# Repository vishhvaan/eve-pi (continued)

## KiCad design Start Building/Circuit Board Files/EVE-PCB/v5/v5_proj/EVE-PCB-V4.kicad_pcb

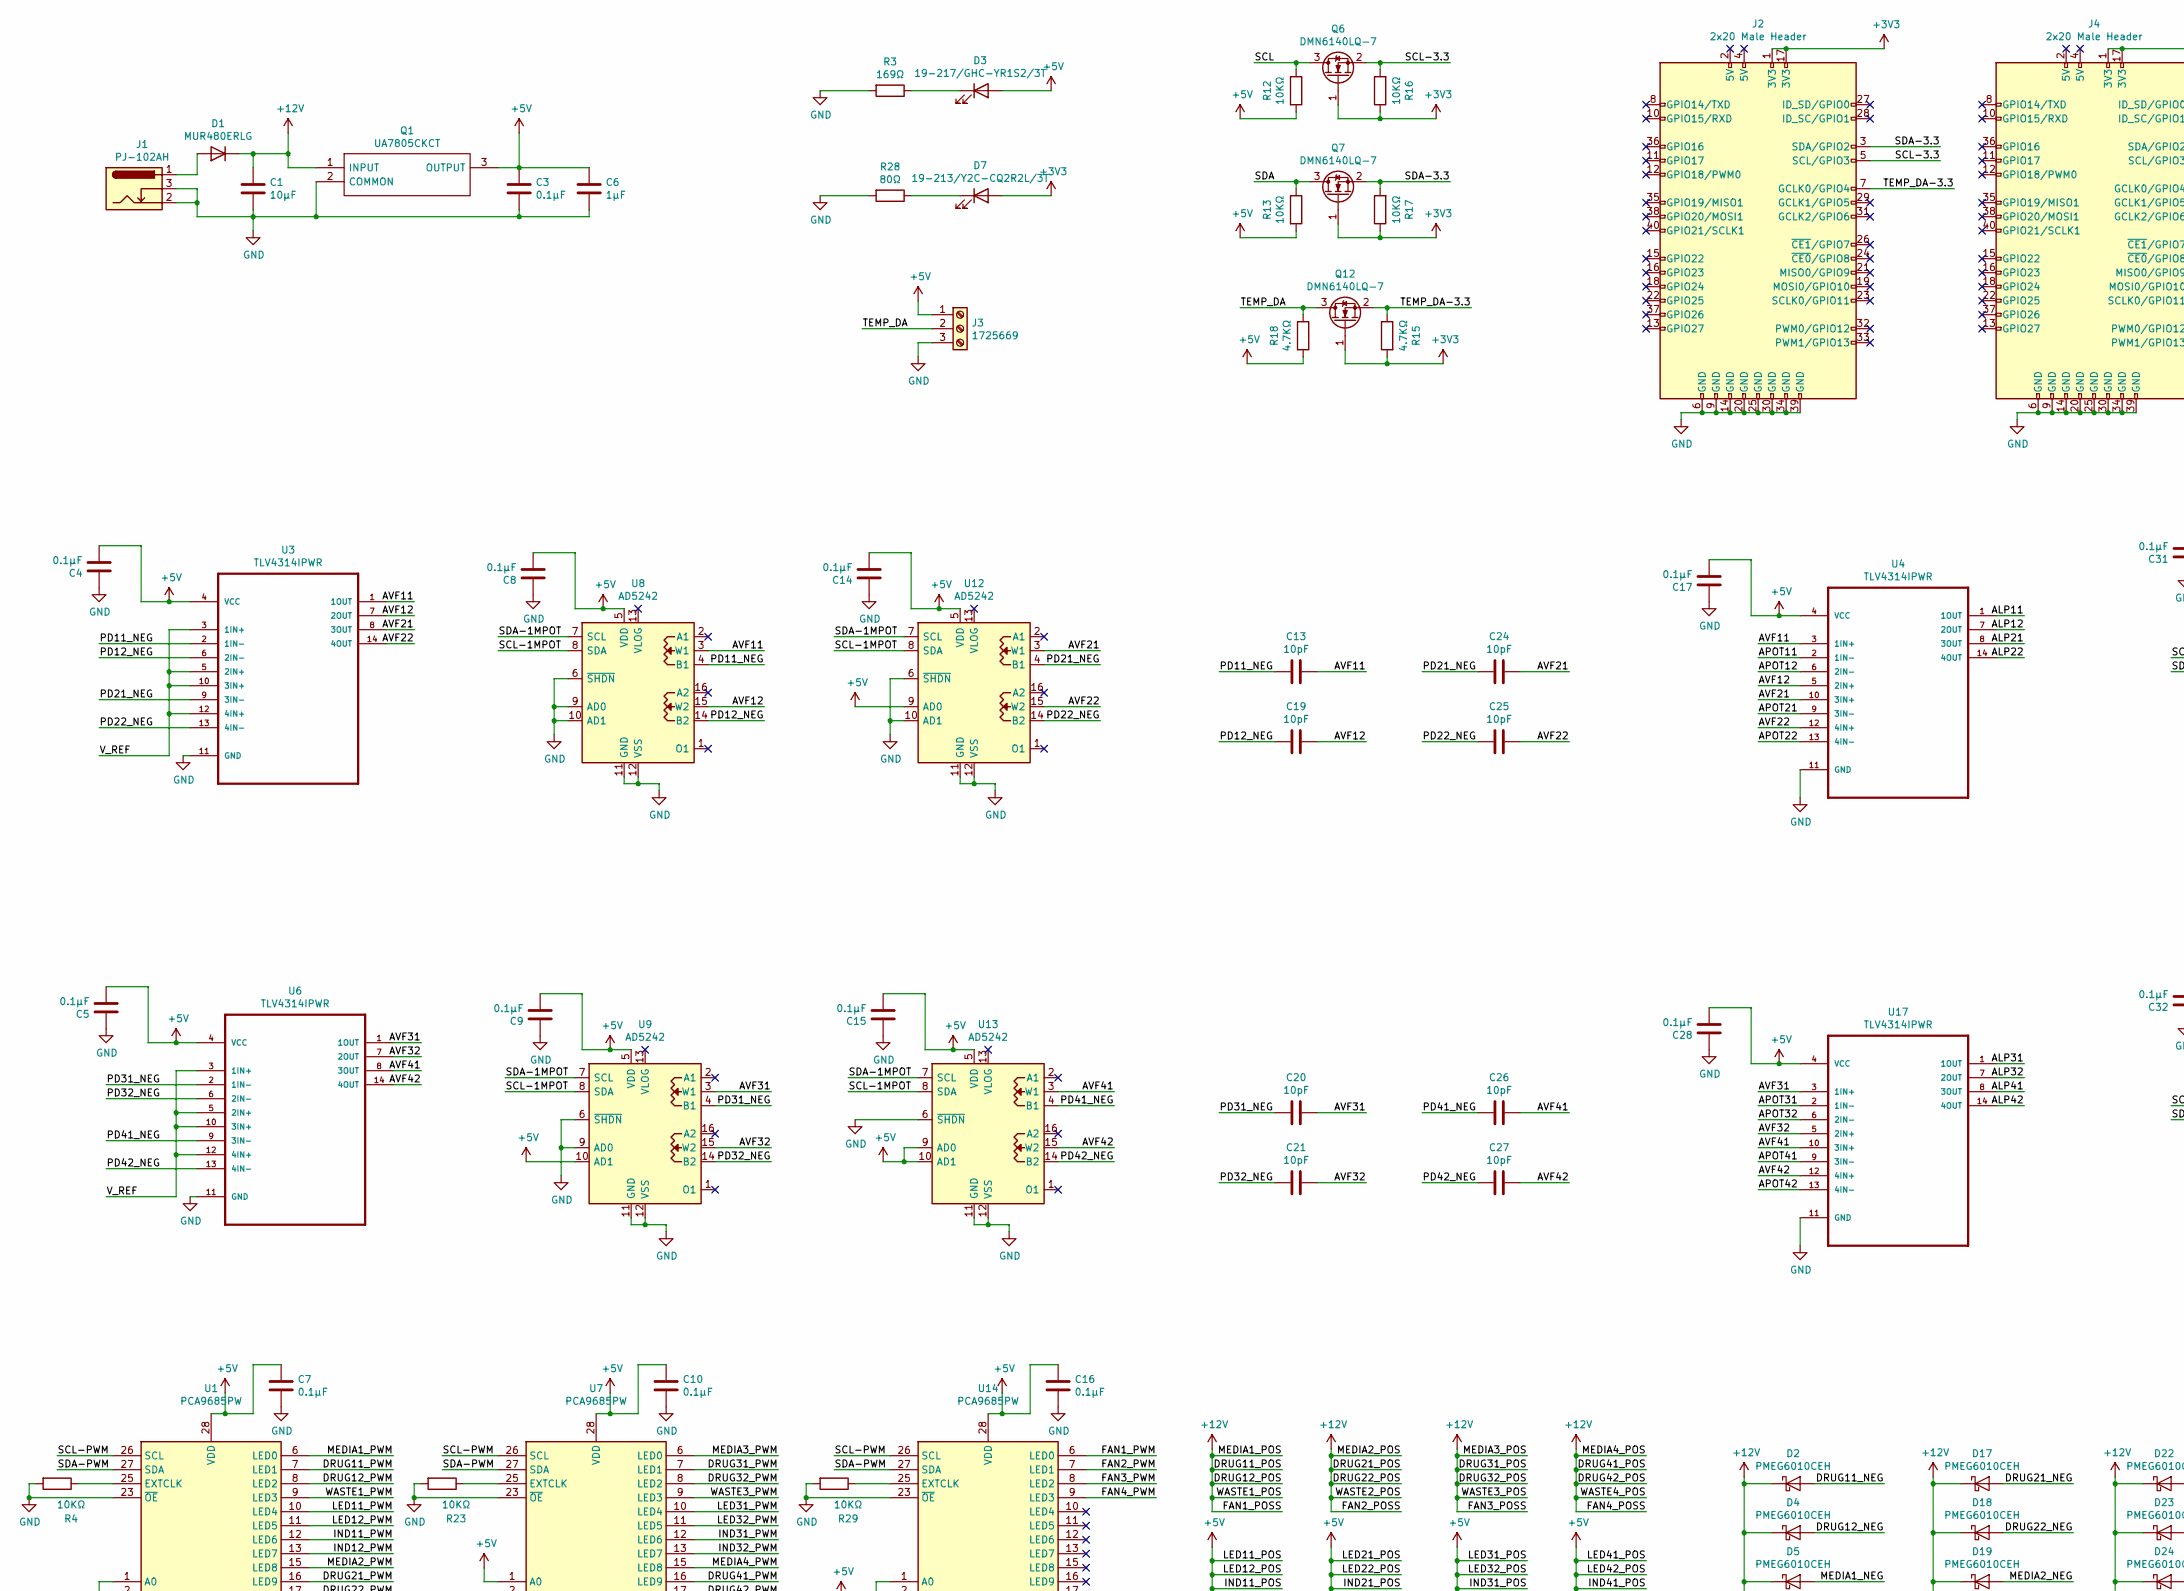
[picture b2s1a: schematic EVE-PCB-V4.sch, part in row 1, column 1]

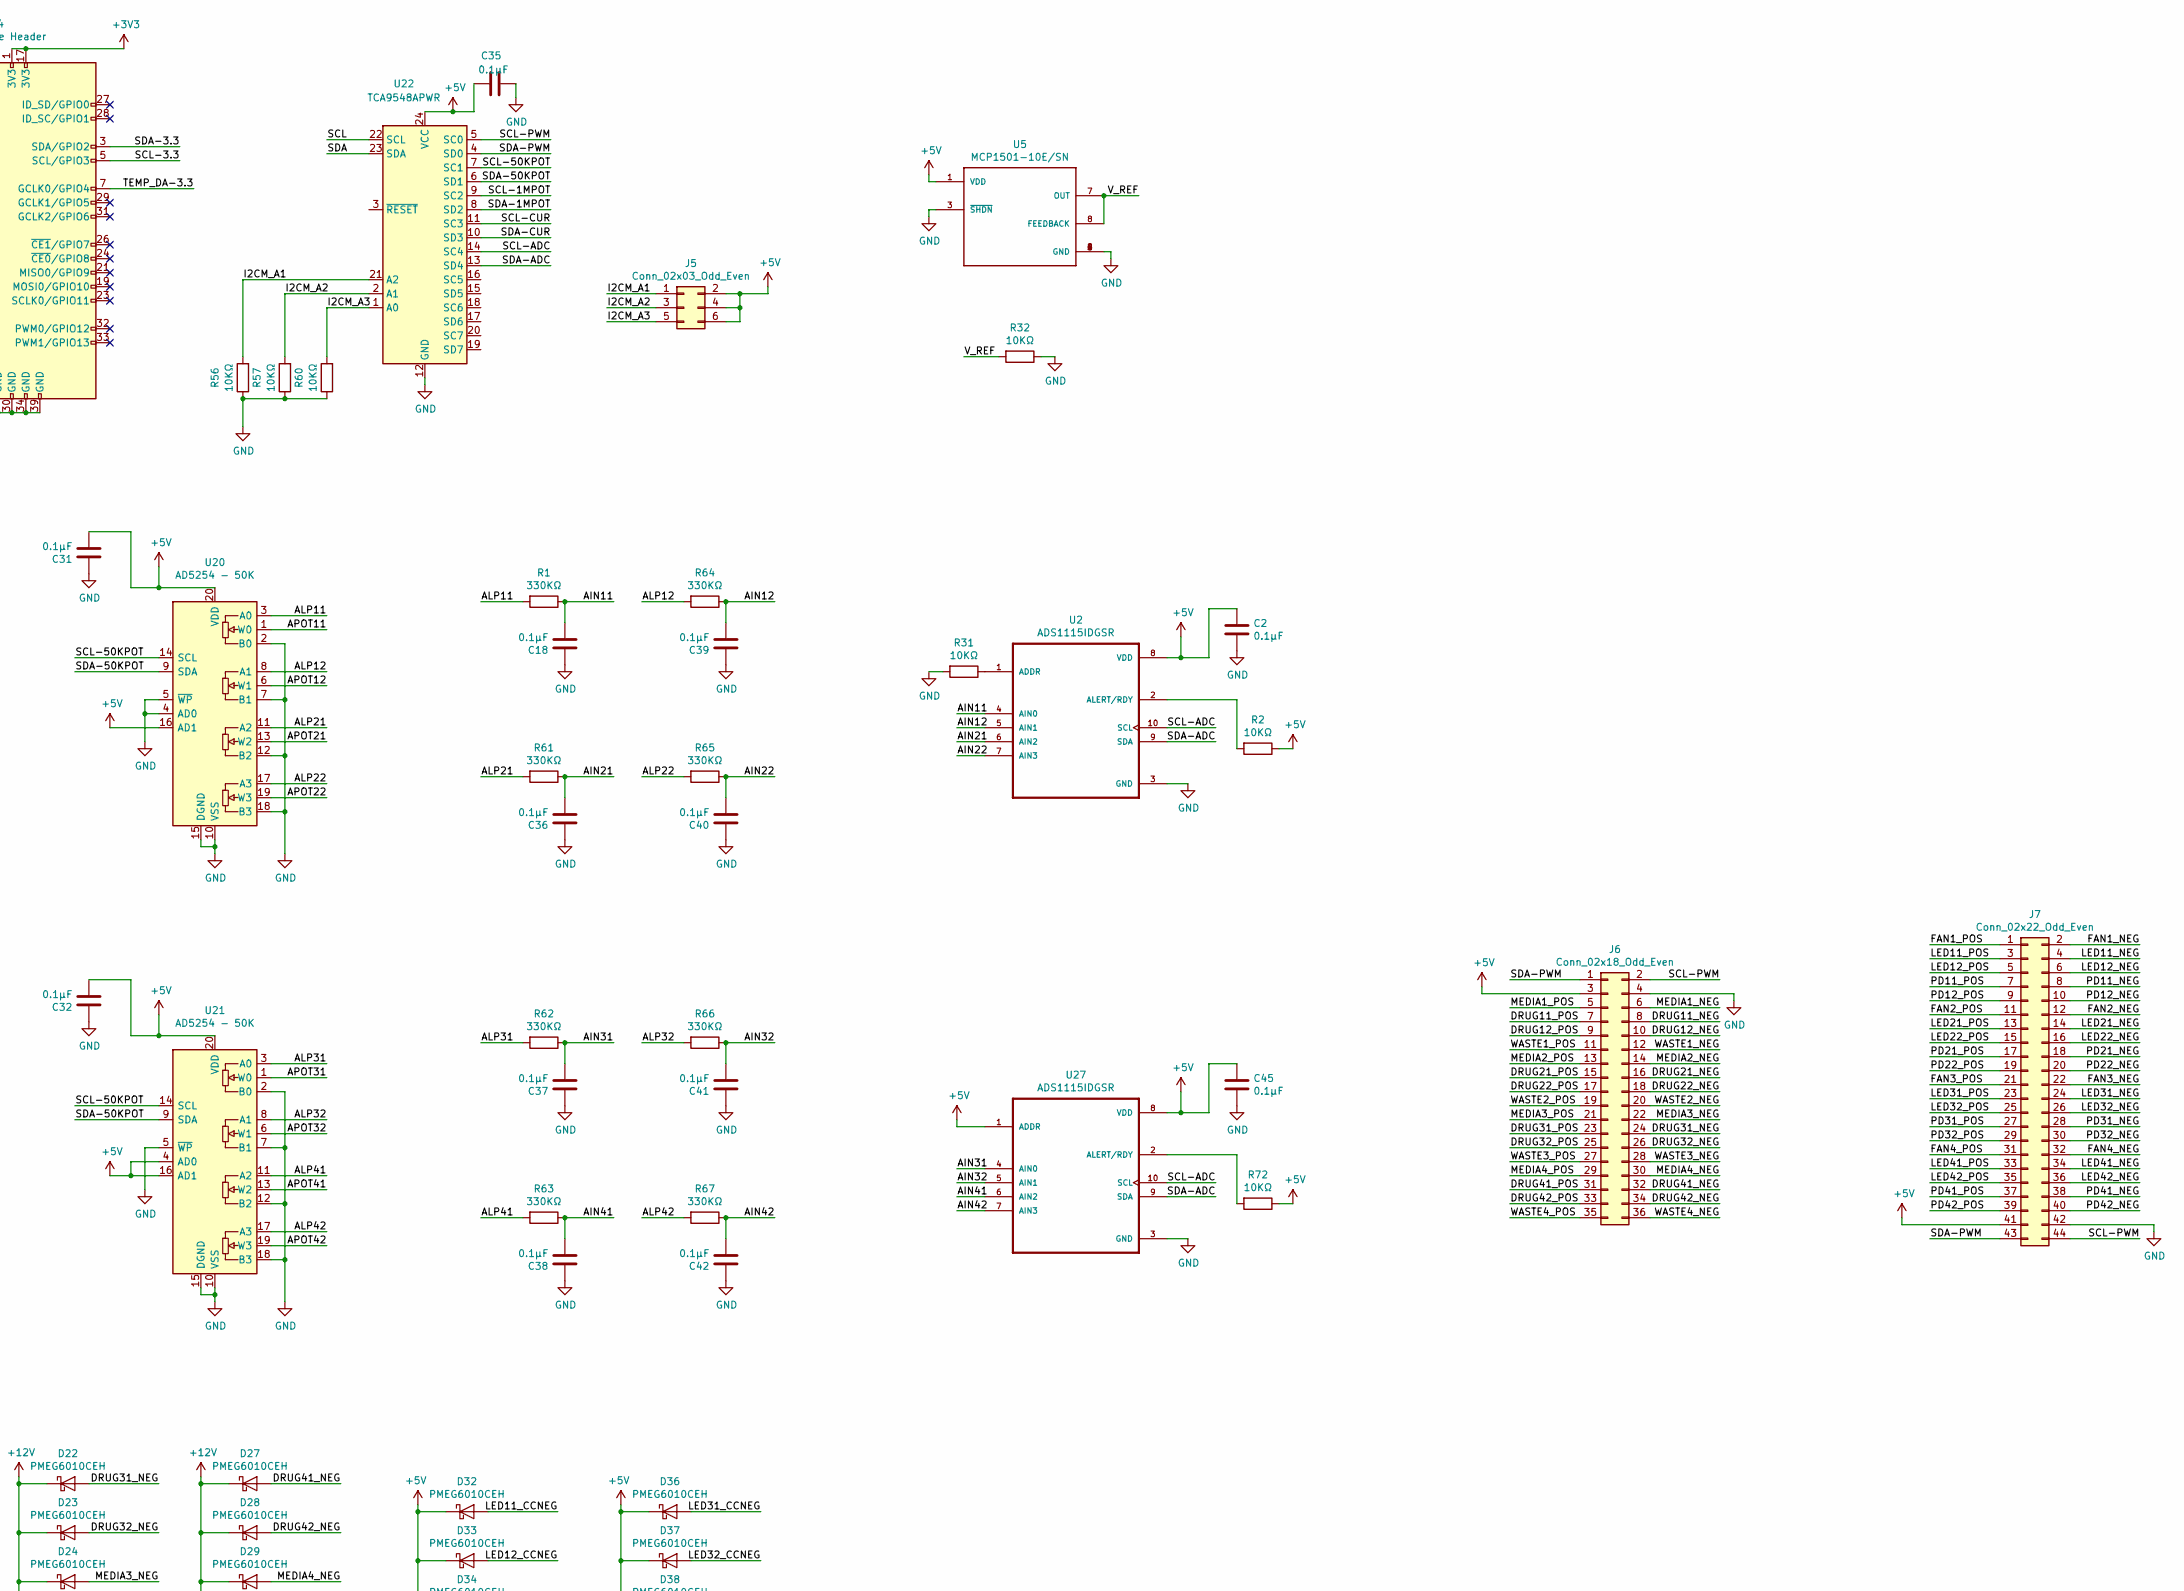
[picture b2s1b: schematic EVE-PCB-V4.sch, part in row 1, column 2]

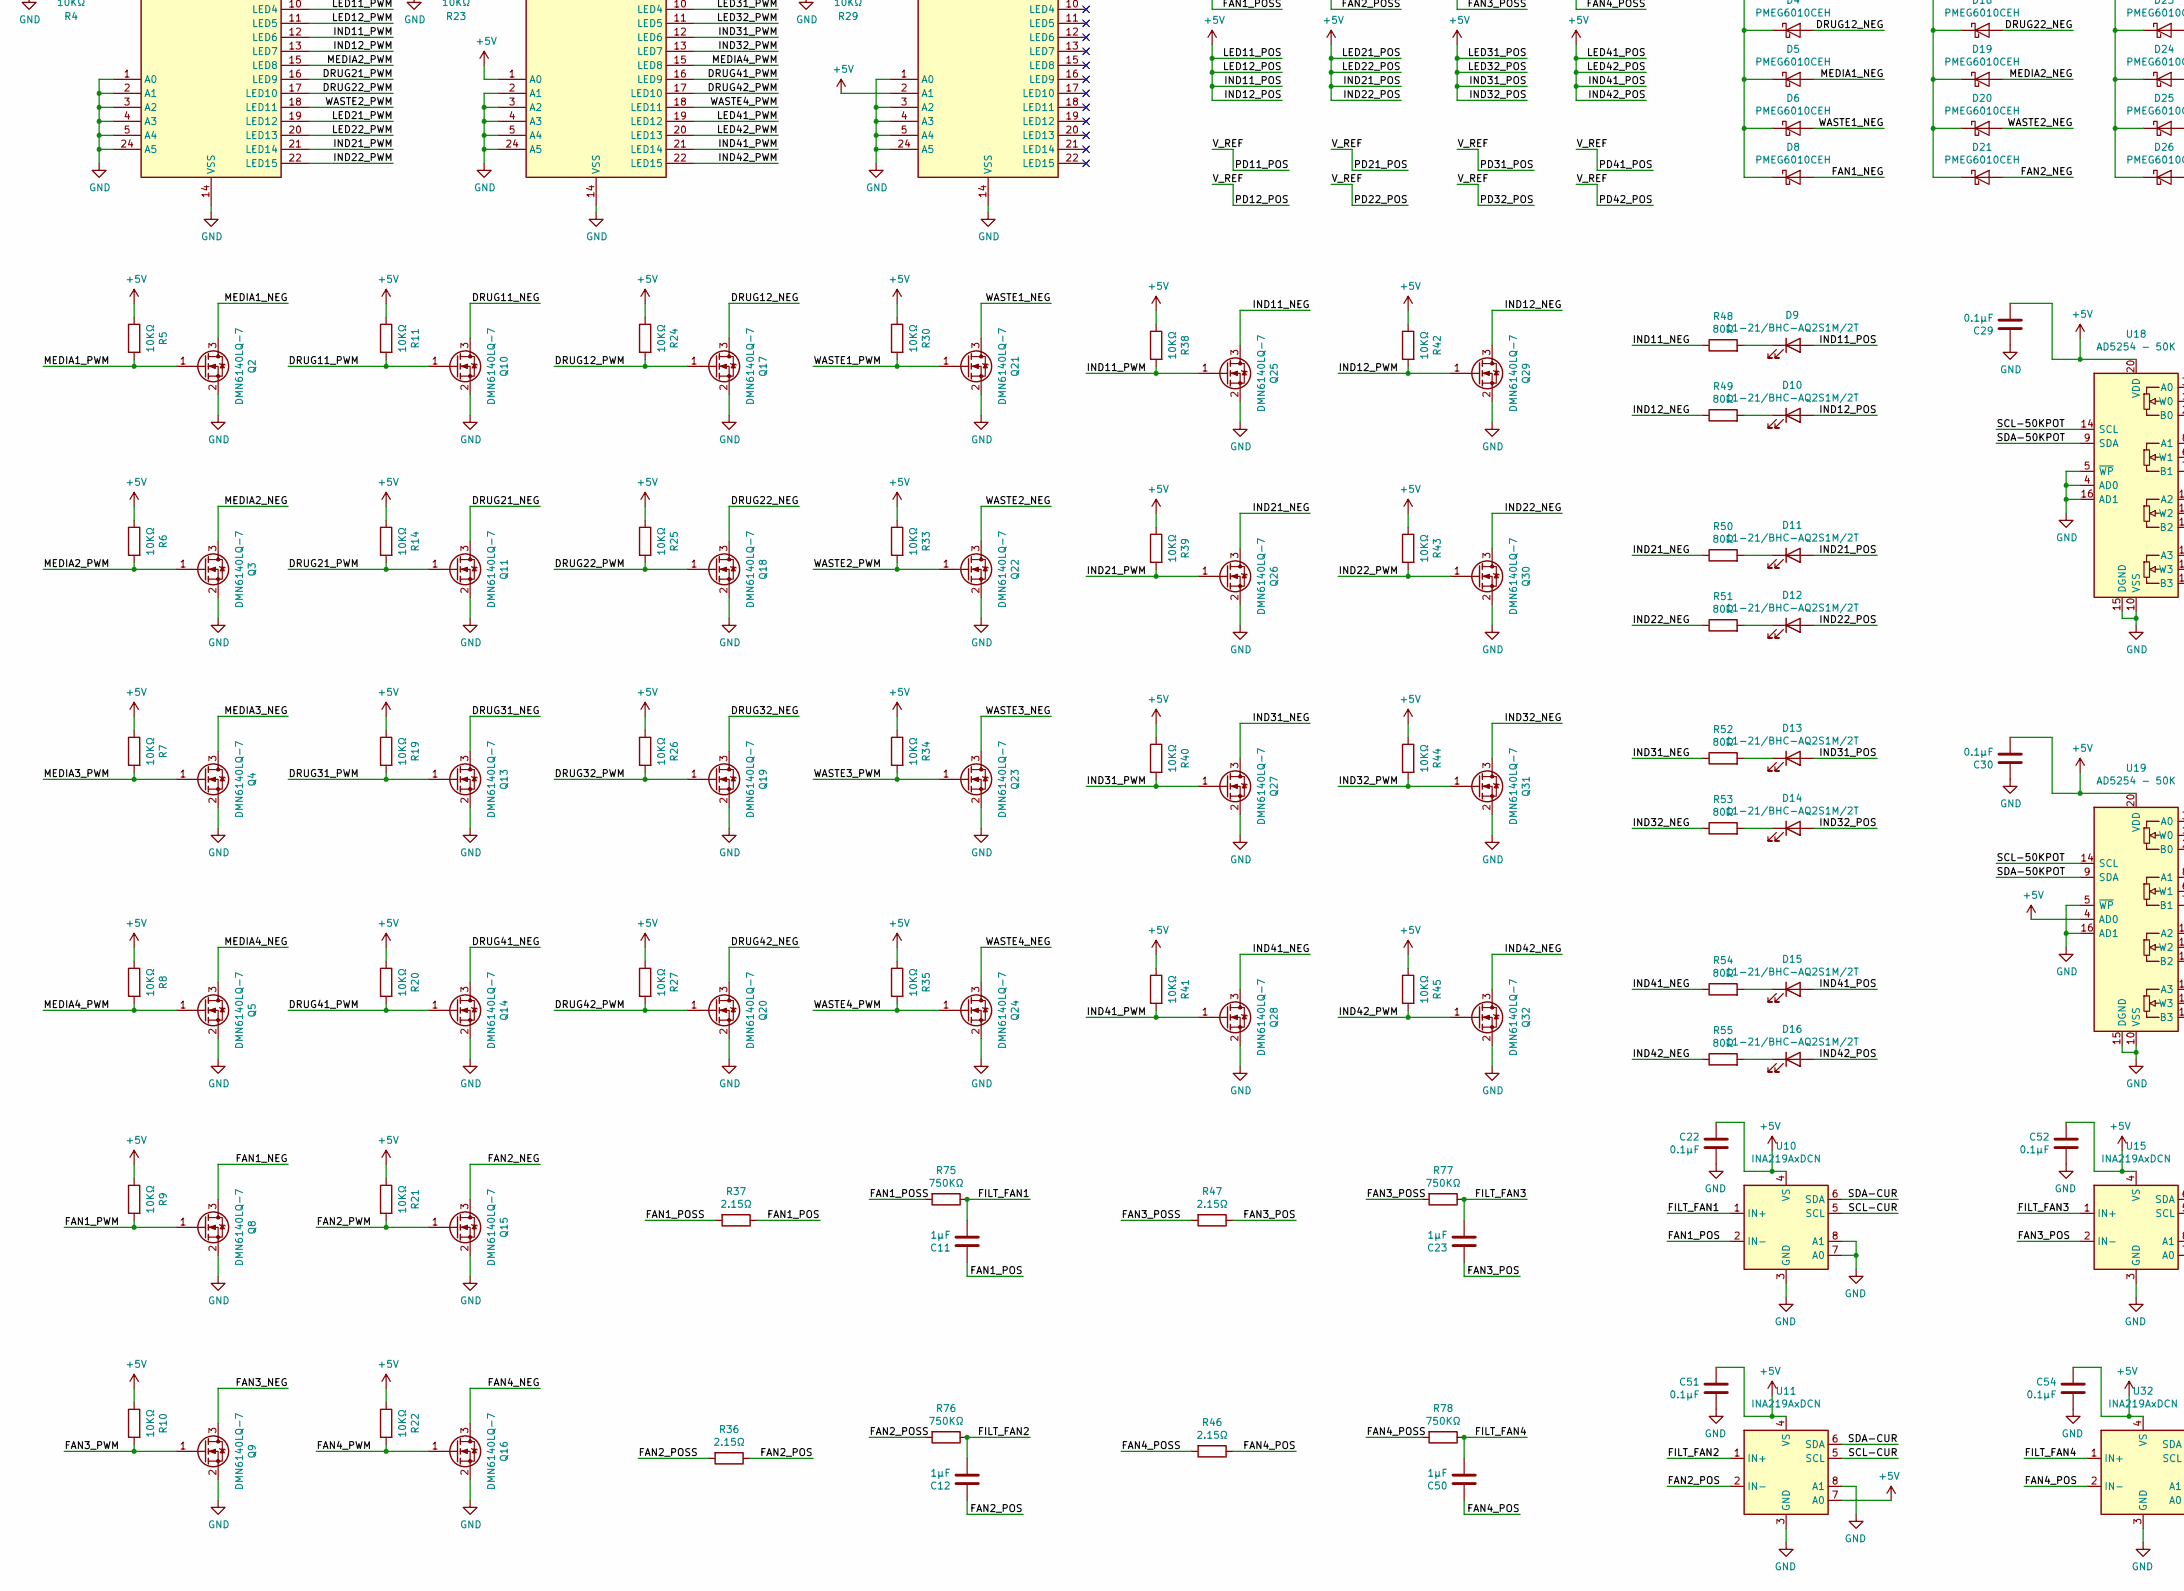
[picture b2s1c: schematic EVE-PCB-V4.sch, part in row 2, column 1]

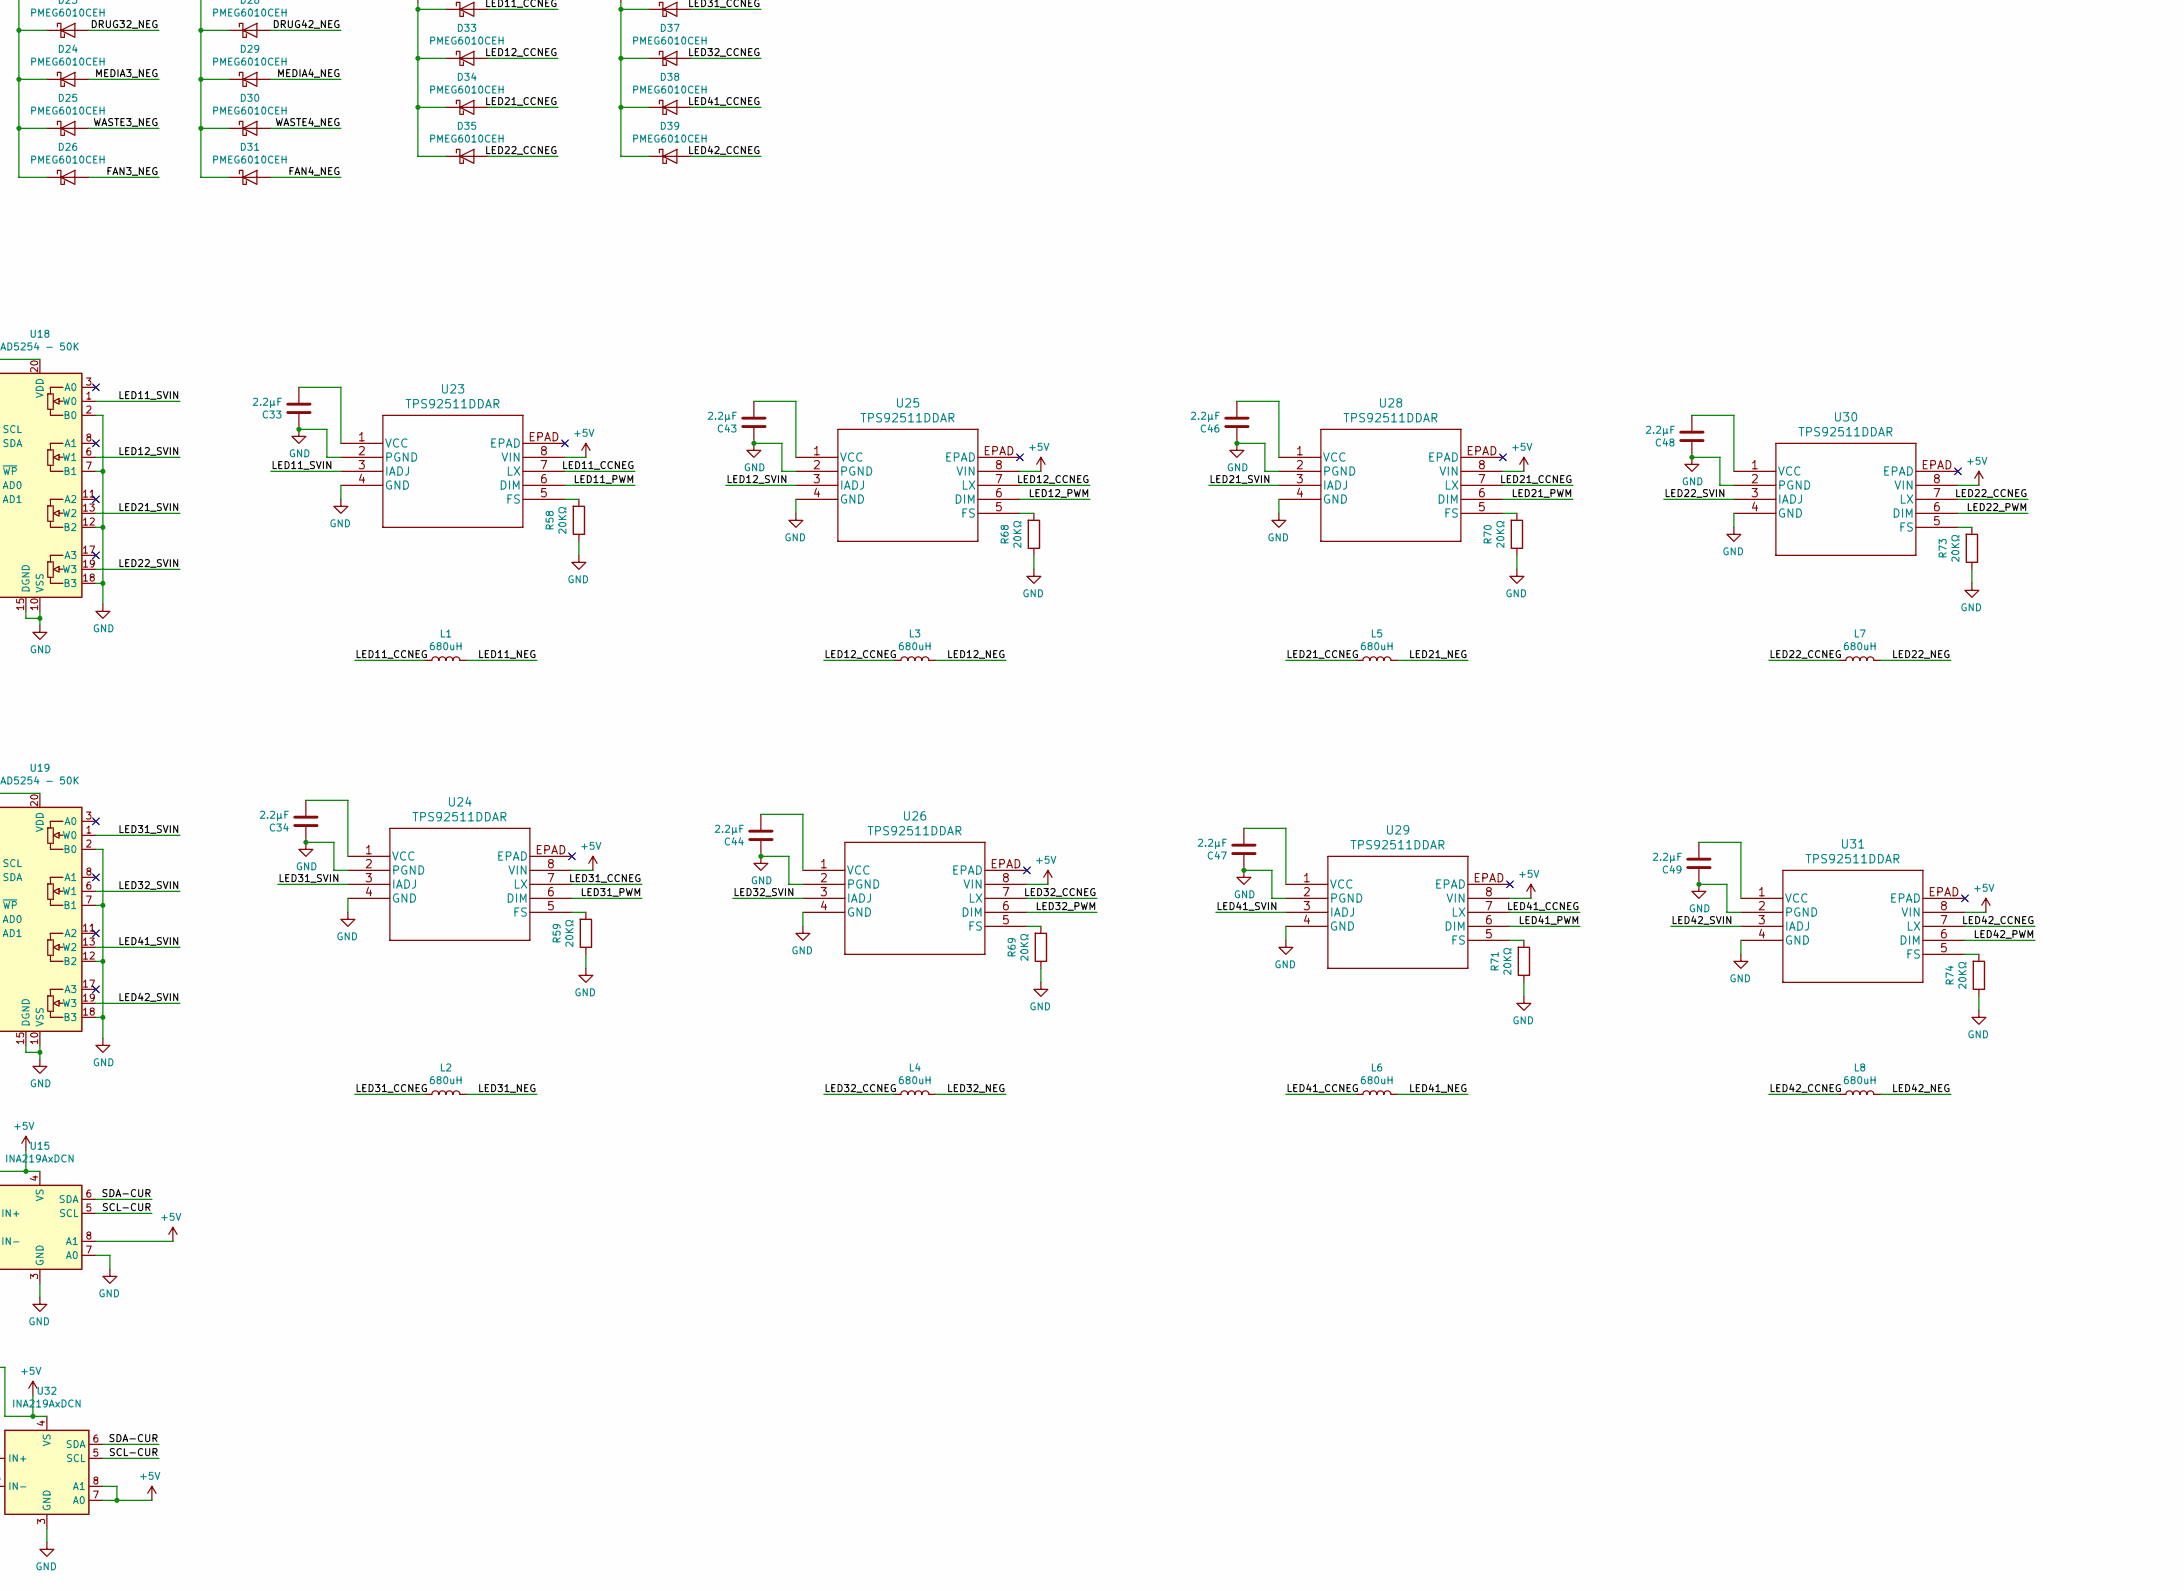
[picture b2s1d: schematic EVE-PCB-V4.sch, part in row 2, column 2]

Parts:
C1: 10μF; C_0805_2012Metric; LCSC C15850
C2, C3, C4, C5, C7, C8, C9, C10, C14, C15, C16, C17, C18, C22, C28, C29, C30, C31, C32, C35, C36, C37, C38, C39, C40, C41, C42, C45, C51, C52, C54: 0.1μF; C_0402_1005Metric; LCSC C1525
C6: 1μF; C_0603_1608Metric; LCSC C5673
C11, C12, C23, C50: 1μF; C_0805_2012Metric; LCSC C28323
C13, C19, C20, C21, C24, C25, C26, C27: 10pF; C_0402_1005Metric; LCSC C32949
C33, C34, C43, C44, C46, C47, C48, C49: 2.2μF; C_0603_1608Metric; LCSC C23630
D1: MUR480ERLG; D_DO-201AE_P3.81mm_Vertical_AnodeUp
D2, D4, D5, D6, D8, D17, D18, D19, D20, D21, D22, D23, D24, D25, D26, D27, D28, D29, D30, D31, D32, D33, D34, D35, D36, D37, D38, D39: PMEG6010CEH; D_SOD-123F; LCSC C110797
D3: 19-217/GHC-YR1S2/3T; LED_0603_1608Metric; LCSC C72043
D7: 19-213/Y2C-CQ2R2L/3T; LED_0603_1608Metric; LCSC C72038
D9, D10, D11, D12, D13, D14, D15, D16: 11-21/BHC-AQ2S1M/2T; LED_1206_3216Metric; LCSC C264323
J1: PJ-102AH; BarrelJack_CUI_PJ-102AH_Horizontal
J2, J4: 2x20 Male Header; PinHeader_2x20_P2.54mm_Vertical
J3: 1725669
J5: Conn_02x03_Odd_Even; PinHeader_2x03_P2.54mm_Vertical
J6: Conn_02x18_Odd_Even; PinHeader_2x18_P2.54mm_Vertical
J7: Conn_02x22_Odd_Even; PinHeader_2x22_P2.54mm_Vertical
L1, L2, L3, L4, L5, L6, L7, L8: 680uH; L_6.3x6.3_H3; LCSC C168101
Q1: UA7805CKCT; TO-220-3_Vertical; Mouser Part Number 595-UA7805CKCT
Q2, Q3, Q4, Q5, Q6, Q7, Q8, Q9, Q10, Q11, Q12, Q13, Q14, Q15, Q16, Q17, Q18, Q19, Q20, Q21, Q22, Q23, Q24, Q25, Q26, Q27, Q28, Q29, Q30, Q31, Q32: DMN6140LQ-7; SOT-23; LCSC C155271
R1, R61, R62, R63, R64, R65, R66, R67: 330KΩ; R_0402_1005Metric; LCSC C25778
R2, R4, R5, R6, R7, R8, R9, R10, R11, R12, R13, R14, R16, R17, R19, R20, R21, R22, R23, R24, R25, R26, R27, R29, R30, R31, R32, R33, R34, R35, R38, R39, R40, R41, R42, R43, R44, R45, R56, R57, R60, R72: 10KΩ; R_0402_1005Metric; LCSC C25744
R3: 169Ω; R_0805_2012Metric; LCSC C17489
R15, R18: 4.7KΩ; R_0402_1005Metric; LCSC C25900
R28, R48, R49, R50, R51, R52, R53, R54, R55: 80Ω; R_0805_2012Metric; LCSC C17833
R36, R37, R46, R47: 2.15Ω; R_1206_3216Metric; LCSC C247507
R58, R59, R68, R69, R70, R71, R73, R74: 20KΩ; R_0402_1005Metric; LCSC C25765
R75, R76, R77, R78: 750KΩ; R_0603_1608Metric; LCSC C23240
U1, U7, U14: PCA9685PW; TSSOP-28_4.4x9.7mm_P0.65mm; LCSC C92206
U2, U27: ADS1115IDGSR; MSOP-10_3x3mm_P0.5mm; LCSC C37593
U3, U4, U6, U17: TLV4314IPWR; TSSOP-14_4.4x5mm_P0.65mm; LCSC C106874
U5: MCP1501-10E/SN; SOIC-8_3.9x4.9mm_P1.27mm
U8, U9, U12, U13: AD5242; TSSOP-16_4.4x5mm_P0.65mm
U10, U11, U15, U32: INA219AxDCN; SOT-23-8; LCSC C87469
U18, U19, U20, U21: AD5254 - 50K; TSSOP-20_4.4x6.5mm_P0.65mm
U22: TCA9548APWR; TSSOP-24_4.4x7.8mm_P0.65mm
U23, U24, U25, U26, U28, U29, U30, U31: TPS92511DDAR; HSOP-8-1EP_3.9x4.9mm_P1.27mm_EP2.41x3.1mm; LCSC C206179

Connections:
+3V3: D7.2 (A), J2.1 (3V3), J2.17 (3V3), J4.1 (3V3), J4.17 (3V3), Q6.1 (G), Q7.1 (G), Q12.1 (G), R15.2, R16.1, R17.1
+5V: C2.1, C3.1, C4.2, C5.2, C6.1, C7.1, C8.2, C9.2, C10.1, C14.2, C15.2, C16.1, C17.2, C22.1, C28.2, C29.2, C30.2, C31.2, C32.2, C35.1, C45.1, C51.1, C52.1, C54.1, D3.2 (A), D9.2 (A), D10.2 (A), D11.2 (A), D12.2 (A), D13.2 (A), D14.2 (A), D15.2 (A), D16.2 (A), D32.1 (K), D33.1 (K), D34.1 (K), D35.1 (K), D36.1 (K), D37.1 (K), D38.1 (K), D39.1 (K), J3.1, J5.2, J5.4, J5.6, J6.3, J7.3, J7.5, J7.13, J7.15, J7.23, J7.25, J7.33, J7.35, J7.41, Q1.3 (OUTPUT), R2.1, R5.1, R6.1, R7.1, R8.1, R9.1, R10.1, R11.1, R12.2, R13.2, R14.1, R18.2, R19.1, R20.1, R21.1, R22.1, R24.1, R25.1, R26.1, R27.1, R30.1, R33.1, R34.1, R35.1, R38.1, R39.1, R40.1, R41.1, R42.1, R43.1, R44.1, R45.1, R72.1, U1.28 (VDD), U2.8 (VDD), U3.4 (VCC), U4.4 (VCC), U5.1 (VDD), U6.4 (VCC), U7.1 (A0), U7.28 (VDD), U8.5 (VDD), U9.5 (VDD), U9.10 (AD1), U10.4 (VS), U11.4 (VS), U11.7 (A0), U12.5 (VDD), U12.9 (AD0), U13.5 (VDD), U13.9 (AD0), U13.10 (AD1), U14.2 (A1), U14.28 (VDD), U15.4 (VS), U15.8 (A1), U17.4 (VCC), U18.20 (VDD), U19.4 (AD0), U19.20 (VDD), U20.16 (AD1), U20.20 (VDD), U21.4 (AD0), U21.16 (AD1), U21.20 (VDD), U22.24 (VCC), U23.8 (VIN), U24.8 (VIN), U25.8 (VIN), U26.8 (VIN), U27.1 (ADDR), U27.8 (VDD), U28.8 (VIN), U29.8 (VIN), U30.8 (VIN), U31.8 (VIN), U32.4 (VS), U32.7 (A0), U32.8 (A1)
+12V: C1.1, D1.1 (K), D2.1 (K), D4.1 (K), D5.1 (K), D6.1 (K), D8.1 (K), D17.1 (K), D18.1 (K), D19.1 (K), D20.1 (K), D21.1 (K), D22.1 (K), D23.1 (K), D24.1 (K), D25.1 (K), D26.1 (K), D27.1 (K), D28.1 (K), D29.1 (K), D30.1 (K), D31.1 (K), J6.5, J6.7, J6.9, J6.11, J6.13, J6.15, J6.17, J6.19, J6.21, J6.23, J6.25, J6.27, J6.29, J6.31, J6.33, J6.35, Q1.1 (INPUT), R36.2, R37.2, R46.2, R47.2, R75.2, R76.2, R77.2, R78.2
/AIN11: C18.2, R1.1, U2.4 (AIN0)
/AIN12: C39.2, R64.1, U2.5 (AIN1)
/AIN21: C36.2, R61.1, U2.6 (AIN2)
/AIN22: C40.2, R65.1, U2.7 (AIN3)
/AIN31: C37.2, R62.1, U27.4 (AIN0)
/AIN32: C41.2, R66.1, U27.5 (AIN1)
/AIN41: C38.2, R63.1, U27.6 (AIN2)
/AIN42: C42.2, R67.1, U27.7 (AIN3)
/ALP11: R1.2, U4.1 (1OUT), U20.3 (A0)
/ALP12: R64.2, U4.7 (2OUT), U20.8 (A1)
/ALP21: R61.2, U4.8 (3OUT), U20.11 (A2)
/ALP22: R65.2, U4.14 (4OUT), U20.17 (A3)
/ALP31: R62.2, U17.1 (1OUT), U21.3 (A0)
/ALP32: R66.2, U17.7 (2OUT), U21.8 (A1)
/ALP41: R63.2, U17.8 (3OUT), U21.11 (A2)
/ALP42: R67.2, U17.14 (4OUT), U21.17 (A3)
/APOT11: U4.2 (1IN-), U20.1 (W0)
/APOT12: U4.6 (2IN-), U20.6 (W1)
/APOT21: U4.9 (3IN-), U20.13 (W2)
/APOT22: U4.13 (4IN-), U20.19 (W3)
/APOT31: U17.2 (1IN-), U21.1 (W0)
/APOT32: U17.6 (2IN-), U21.6 (W1)
/APOT41: U17.9 (3IN-), U21.13 (W2)
/APOT42: U17.13 (4IN-), U21.19 (W3)
/AVF11: C13.1, U3.1 (1OUT), U4.3 (1IN+), U8.3 (W1)
/AVF12: C19.1, U3.7 (2OUT), U4.5 (2IN+), U8.15 (W2)
/AVF21: C24.1, U3.8 (3OUT), U4.10 (3IN+), U12.3 (W1)
/AVF22: C25.1, U3.14 (4OUT), U4.12 (4IN+), U12.15 (W2)
/AVF31: C20.1, U6.1 (1OUT), U9.3 (W1), U17.3 (1IN+)
/AVF32: C21.1, U6.7 (2OUT), U9.15 (W2), U17.5 (2IN+)
/AVF41: C26.1, U6.8 (3OUT), U13.3 (W1), U17.10 (3IN+)
/AVF42: C27.1, U6.14 (4OUT), U13.15 (W2), U17.12 (4IN+)
/DRUG11_NEG: D2.2 (A), J6.8, Q10.3 (D)
/DRUG11_PWM: Q10.1 (G), R11.2, U1.7 (LED1)
/DRUG12_NEG: D4.2 (A), J6.10, Q17.3 (D)
/DRUG12_PWM: Q17.1 (G), R24.2, U1.8 (LED2)
/DRUG21_NEG: D17.2 (A), J6.16, Q11.3 (D)
/DRUG21_PWM: Q11.1 (G), R14.2, U1.16 (LED9)
/DRUG22_NEG: D18.2 (A), J6.18, Q18.3 (D)
/DRUG22_PWM: Q18.1 (G), R25.2, U1.17 (LED10)
/DRUG31_NEG: D22.2 (A), J6.24, Q13.3 (D)
/DRUG31_PWM: Q13.1 (G), R19.2, U7.7 (LED1)
/DRUG32_NEG: D23.2 (A), J6.26, Q19.3 (D)
/DRUG32_PWM: Q19.1 (G), R26.2, U7.8 (LED2)
/DRUG41_NEG: D27.2 (A), J6.32, Q14.3 (D)
/DRUG41_PWM: Q14.1 (G), R20.2, U7.16 (LED9)
/DRUG42_NEG: D28.2 (A), J6.34, Q20.3 (D)
/DRUG42_PWM: Q20.1 (G), R27.2, U7.17 (LED10)
/FAN1_NEG: D8.2 (A), J7.2, Q8.3 (D)
/FAN1_POS: C11.1, J7.1, R37.1, U10.2 (IN-)
/FAN1_PWM: Q8.1 (G), R9.2, U14.6 (LED0)
/FAN2_NEG: D21.2 (A), J7.12, Q15.3 (D)
/FAN2_POS: C12.1, J7.11, R36.1, U11.2 (IN-)
/FAN2_PWM: Q15.1 (G), R21.2, U14.7 (LED1)
/FAN3_NEG: D26.2 (A), J7.22, Q9.3 (D)
/FAN3_POS: C23.1, J7.21, R47.1, U15.2 (IN-)
/FAN3_PWM: Q9.1 (G), R10.2, U14.8 (LED2)
/FAN4_NEG: D31.2 (A), J7.32, Q16.3 (D)
/FAN4_POS: C50.1, J7.31, R46.1, U32.2 (IN-)
/FAN4_PWM: Q16.1 (G), R22.2, U14.9 (LED3)
/FILT_FAN1: C11.2, R75.1, U10.1 (IN+)
/FILT_FAN2: C12.2, R76.1, U11.1 (IN+)
/FILT_FAN3: C23.2, R77.1, U15.1 (IN+)
/FILT_FAN4: C50.2, R78.1, U32.1 (IN+)
/I2CM_A1: J5.1, R56.2, U22.21 (A2)
/I2CM_A2: J5.3, R57.2, U22.2 (A1)
/I2CM_A3: J5.5, R60.2, U22.1 (A0)
/IND11_NEG: Q25.3 (D), R48.1
/IND11_PWM: Q25.1 (G), R38.2, U1.12 (LED6)
/IND12_NEG: Q29.3 (D), R49.1
/IND12_PWM: Q29.1 (G), R42.2, U1.13 (LED7)
/IND21_NEG: Q26.3 (D), R50.1
/IND21_PWM: Q26.1 (G), R39.2, U1.21 (LED14)
/IND22_NEG: Q30.3 (D), R51.1
/IND22_PWM: Q30.1 (G), R43.2, U1.22 (LED15)
/IND31_NEG: Q27.3 (D), R52.1
/IND31_PWM: Q27.1 (G), R40.2, U7.12 (LED6)
/IND32_NEG: Q31.3 (D), R53.1
/IND32_PWM: Q31.1 (G), R44.2, U7.13 (LED7)
/IND41_NEG: Q28.3 (D), R54.1
/IND41_PWM: Q28.1 (G), R41.2, U7.21 (LED14)
/IND42_NEG: Q32.3 (D), R55.1
/IND42_PWM: Q32.1 (G), R45.2, U7.22 (LED15)
/LED11_CCNEG: D32.2 (A), L1.1, U23.7 (LX)
/LED11_NEG: J7.4, L1.2
/LED11_PWM: U1.10 (LED4), U23.6 (DIM)
/LED11_SVIN: U18.1 (W0), U23.3 (IADJ)
/LED12_CCNEG: D33.2 (A), L3.1, U25.7 (LX)
/LED12_NEG: J7.6, L3.2
/LED12_PWM: U1.11 (LED5), U25.6 (DIM)
/LED12_SVIN: U18.6 (W1), U25.3 (IADJ)
/LED21_CCNEG: D34.2 (A), L5.1, U28.7 (LX)
/LED21_NEG: J7.14, L5.2
/LED21_PWM: U1.19 (LED12), U28.6 (DIM)
/LED21_SVIN: U18.13 (W2), U28.3 (IADJ)
/LED22_CCNEG: D35.2 (A), L7.1, U30.7 (LX)
/LED22_NEG: J7.16, L7.2
/LED22_PWM: U1.20 (LED13), U30.6 (DIM)
/LED22_SVIN: U18.19 (W3), U30.3 (IADJ)
/LED31_CCNEG: D36.2 (A), L2.1, U24.7 (LX)
/LED31_NEG: J7.24, L2.2
/LED31_PWM: U7.10 (LED4), U24.6 (DIM)
/LED31_SVIN: U19.1 (W0), U24.3 (IADJ)
/LED32_CCNEG: D37.2 (A), L4.1, U26.7 (LX)
/LED32_NEG: J7.26, L4.2
/LED32_PWM: U7.11 (LED5), U26.6 (DIM)
/LED32_SVIN: U19.6 (W1), U26.3 (IADJ)
/LED41_CCNEG: D38.2 (A), L6.1, U29.7 (LX)
/LED41_NEG: J7.34, L6.2
/LED41_PWM: U7.19 (LED12), U29.6 (DIM)
/LED41_SVIN: U19.13 (W2), U29.3 (IADJ)
/LED42_CCNEG: D39.2 (A), L8.1, U31.7 (LX)
/LED42_NEG: J7.36, L8.2
/LED42_PWM: U7.20 (LED13), U31.6 (DIM)
/LED42_SVIN: U19.19 (W3), U31.3 (IADJ)
/MEDIA1_NEG: D5.2 (A), J6.6, Q2.3 (D)
/MEDIA1_PWM: Q2.1 (G), R5.2, U1.6 (LED0)
/MEDIA2_NEG: D19.2 (A), J6.14, Q3.3 (D)
/MEDIA2_PWM: Q3.1 (G), R6.2, U1.15 (LED8)
/MEDIA3_NEG: D24.2 (A), J6.22, Q4.3 (D)
/MEDIA3_PWM: Q4.1 (G), R7.2, U7.6 (LED0)
/MEDIA4_NEG: D29.2 (A), J6.30, Q5.3 (D)
/MEDIA4_PWM: Q5.1 (G), R8.2, U7.15 (LED8)
/PD11_NEG: C13.2, J7.8, U3.2 (1IN-), U8.4 (B1)
/PD11_POS: J7.7, J7.9, J7.17, J7.19, J7.27, J7.29, J7.37, J7.39, R32.2, U3.3 (1IN+), U3.5 (2IN+), U3.10 (3IN+), U3.12 (4IN+), U5.7 (OUT), U5.8 (FEEDBACK), U6.3 (1IN+), U6.5 (2IN+), U6.10 (3IN+), U6.12 (4IN+)
/PD12_NEG: C19.2, J7.10, U3.6 (2IN-), U8.14 (B2)
/PD21_NEG: C24.2, J7.18, U3.9 (3IN-), U12.4 (B1)
/PD22_NEG: C25.2, J7.20, U3.13 (4IN-), U12.14 (B2)
/PD31_NEG: C20.2, J7.28, U6.2 (1IN-), U9.4 (B1)
/PD32_NEG: C21.2, J7.30, U6.6 (2IN-), U9.14 (B2)
/PD41_NEG: C26.2, J7.38, U6.9 (3IN-), U13.4 (B1)
/PD42_NEG: C27.2, J7.40, U6.13 (4IN-), U13.14 (B2)
/SCL: Q6.3 (D), R12.1, U22.22 (SCL)
/SCL-1MPOT: U8.8 (SDA), U9.8 (SDA), U12.8 (SDA), U13.8 (SDA), U22.9 (SC2)
/SCL-3.3: J2.5 (SCL/GPIO3), J4.5 (SCL/GPIO3), Q6.2 (S), R16.2
/SCL-50KPOT: U18.14 (SCL), U19.14 (SCL), U20.14 (SCL), U21.14 (SCL), U22.7 (SC1)
/SCL-ADC: U2.10 (SCL), U22.14 (SC4), U27.10 (SCL)
/SCL-CUR: U10.5 (SCL), U11.5 (SCL), U15.5 (SCL), U22.11 (SC3), U32.5 (SCL)
/SCL-PWM: J6.2, J7.44, U1.26 (SCL), U7.26 (SCL), U14.26 (SCL), U22.5 (SC0)
/SDA: Q7.3 (D), R13.1, U22.23 (SDA)
/SDA-1MPOT: U8.7 (SCL), U9.7 (SCL), U12.7 (SCL), U13.7 (SCL), U22.8 (SD2)
/SDA-3.3: J2.3 (SDA/GPIO2), J4.3 (SDA/GPIO2), Q7.2 (S), R17.2
/SDA-50KPOT: U18.9 (SDA), U19.9 (SDA), U20.9 (SDA), U21.9 (SDA), U22.6 (SD1)
/SDA-ADC: U2.9 (SDA), U22.13 (SD4), U27.9 (SDA)
/SDA-CUR: U10.6 (SDA), U11.6 (SDA), U15.6 (SDA), U22.10 (SD3), U32.6 (SDA)
/SDA-PWM: J6.1, J7.43, U1.27 (SDA), U7.27 (SDA), U14.27 (SDA), U22.4 (SD0)
/TEMP_DA: J3.2, Q12.3 (D), R18.1
/TEMP_DA-3.3: J2.7 (GCLK0/GPIO4), J4.7 (GCLK0/GPIO4), Q12.2 (S), R15.1
/WASTE1_NEG: D6.2 (A), J6.12, Q21.3 (D)
/WASTE1_PWM: Q21.1 (G), R30.2, U1.9 (LED3)
/WASTE2_NEG: D20.2 (A), J6.20, Q22.3 (D)
/WASTE2_PWM: Q22.1 (G), R33.2, U1.18 (LED11)
/WASTE3_NEG: D25.2 (A), J6.28, Q23.3 (D)
/WASTE3_PWM: Q23.1 (G), R34.2, U7.9 (LED3)
/WASTE4_NEG: D30.2 (A), J6.36, Q24.3 (D)
/WASTE4_PWM: Q24.1 (G), R35.2, U7.18 (LED11)
GND: C1.2, C2.2, C3.2, C4.1, C5.1, C6.2, C7.2, C8.1, C9.1, C10.2, C14.1, C15.1, C16.2, C17.1, C18.1, C22.2, C28.1, C29.1, C30.1, C31.1, C32.1, C33.1, C34.1, C35.2, C36.1, C37.1, C38.1, C39.1, C40.1, C41.1, C42.1, C43.1, C44.1, C45.2, C46.1, C47.1, C48.1, C49.1, C51.2, C52.2, C54.2, J1.2, J1.3, J2.6 (GND), J2.9 (GND), J2.14 (GND), J2.20 (GND), J2.25 (GND), J2.30 (GND), J2.34 (GND), J2.39 (GND), J3.3, J4.6 (GND), J4.9 (GND), J4.14 (GND), J4.20 (GND), J4.25 (GND), J4.30 (GND), J4.34 (GND), J4.39 (GND), J6.4, J7.42, Q1.2 (COMMON), Q2.2 (S), Q3.2 (S), Q4.2 (S), Q5.2 (S), Q8.2 (S), Q9.2 (S), Q10.2 (S), Q11.2 (S), Q13.2 (S), Q14.2 (S), Q15.2 (S), Q16.2 (S), Q17.2 (S), Q18.2 (S), Q19.2 (S), Q20.2 (S), Q21.2 (S), Q22.2 (S), Q23.2 (S), Q24.2 (S), Q25.2 (S), Q26.2 (S), Q27.2 (S), Q28.2 (S), Q29.2 (S), Q30.2 (S), Q31.2 (S), Q32.2 (S), R3.2, R4.2, R23.2, R28.2, R29.2, R31.2, R32.1, R56.1, R57.1, R58.1, R59.1, R60.1, R68.1, R69.1, R70.1, R71.1, R73.1, R74.1, U1.1 (A0), U1.2 (A1), U1.3 (A2), U1.4 (A3), U1.5 (A4), U1.14 (VSS), U1.23 (~OE), U1.24 (A5), U2.3 (GND), U3.11 (GND), U4.11 (GND), U5.2 (GND), U5.3 (~SHDN~), U5.4 (GND), U5.5 (GND), U5.6 (GND), U6.11 (GND), U7.2 (A1), U7.3 (A2), U7.4 (A3), U7.5 (A4), U7.14 (VSS), U7.23 (~OE), U7.24 (A5), U8.6 (~SHDN~), U8.9 (AD0), U8.10 (AD1), U8.11 (GND), U8.12 (VSS), U9.6 (~SHDN~), U9.9 (AD0), U9.11 (GND), U9.12 (VSS), U10.3 (GND), U10.7 (A0), U10.8 (A1), U11.3 (GND), U11.8 (A1), U12.6 (~SHDN~), U12.10 (AD1), U12.11 (GND), U12.12 (VSS), U13.6 (~SHDN~), U13.11 (GND), U13.12 (VSS), U14.1 (A0), U14.3 (A2), U14.4 (A3), U14.5 (A4), U14.14 (VSS), U14.23 (~OE), U14.24 (A5), U15.3 (GND), U15.7 (A0), U17.11 (GND), U18.2 (B0), U18.4 (AD0), U18.5 (~WP~), U18.7 (B1), U18.10 (VSS), U18.12 (B2), U18.15 (DGND), U18.16 (AD1), U18.18 (B3), U19.2 (B0), U19.5 (~WP~), U19.7 (B1), U19.10 (VSS), U19.12 (B2), U19.15 (DGND), U19.16 (AD1), U19.18 (B3), U20.2 (B0), U20.4 (AD0), U20.5 (~WP~), U20.7 (B1), U20.10 (VSS), U20.12 (B2), U20.15 (DGND), U20.18 (B3), U21.2 (B0), U21.5 (~WP~), U21.7 (B1), U21.10 (VSS), U21.12 (B2), U21.15 (DGND), U21.18 (B3), U22.12 (GND), U23.2 (PGND), U23.4 (GND), U24.2 (PGND), U24.4 (GND), U25.2 (PGND), U25.4 (GND), U26.2 (PGND), U26.4 (GND), U27.3 (GND), U28.2 (PGND), U28.4 (GND), U29.2 (PGND), U29.4 (GND), U30.2 (PGND), U30.4 (GND), U31.2 (PGND), U31.4 (GND), U32.3 (GND)
unnamed: C33.2, U23.1 (VCC)
unnamed: C34.2, U24.1 (VCC)
unnamed: C43.2, U25.1 (VCC)
unnamed: C44.2, U26.1 (VCC)
unnamed: C46.2, U28.1 (VCC)
unnamed: C47.2, U29.1 (VCC)
unnamed: C48.2, U30.1 (VCC)
unnamed: C49.2, U31.1 (VCC)
unnamed: D1.2 (A), J1.1
unnamed: D3.1 (K), R3.1
unnamed: D7.1 (K), R28.1
unnamed: D9.1 (K), R48.2
unnamed: D10.1 (K), R49.2
unnamed: D11.1 (K), R50.2
unnamed: D12.1 (K), R51.2
unnamed: D13.1 (K), R52.2
unnamed: D14.1 (K), R53.2
unnamed: D15.1 (K), R54.2
unnamed: D16.1 (K), R55.2
unnamed: R2.2, U2.2 (ALERT/RDY)
unnamed: R4.1, U1.25 (EXTCLK)
unnamed: R23.1, U7.25 (EXTCLK)
unnamed: R29.1, U14.25 (EXTCLK)
unnamed: R31.1, U2.1 (ADDR)
unnamed: R58.2, U23.5 (FS)
unnamed: R59.2, U24.5 (FS)
unnamed: R68.2, U25.5 (FS)
unnamed: R69.2, U26.5 (FS)
unnamed: R70.2, U28.5 (FS)
unnamed: R71.2, U29.5 (FS)
unnamed: R72.2, U27.2 (ALERT/RDY)
unnamed: R73.2, U30.5 (FS)
unnamed: R74.2, U31.5 (FS)
